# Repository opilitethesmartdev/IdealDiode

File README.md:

# Ideal Diode
Author: opilitethesmartdev

This is a small PCB featuring an ideal diode emulator using a comparator and a P-MOSFET.

# Principle

1. It uses two diodes to let power in from any side without connecting them, used to feed the comparator and the voltages for the MOSFETS
2. a P-MOS sits between the diodes, with its internal diode directed at the side to be blocked.
3. This P-MOS is pulled high by the same two diodes from #1
4. An N-MOS sits below the P-MOS gate, and will pull it down when activated (turning the P-MOS on)
5. A comparator compares the two sides, and when the forward side is higher than the reverse side, it pulls its output high,
activating the N-MOS, which pulls the P-MOS down, which lets current flow

# Performance
The performance of such constructs is dependent on the P-MOS they use - for simulation, I have used the specs of an DMP3099L P-MOS
(~100mOhm Rdson at -5V), which yield about a 0.1V drop at 1A current - much lower for smaller currents.
However, this PCB component uses the AO3401A, which has a much lower RDSon (about 45 mOhm at the same voltage)

# Simulation
I used Falstad for the simulation. [Here is the link](https://www.falstad.com/circuit/circuitjs.html?ctz=DwYwlgTgBAZgvAIgIwKgFwM6IAwDpsEECsqYIiSeATAVQOx0DM2AHFQGwCcndqIARoiLZUAB0EIALI1QA3CENQBbTEICmAWiQoAfACgoUYAHcoAD0RN2UFpJZQrNliNg4EAen2HgAYQD2SqIAhhBBaH7QFgjskthOcTFxLEjsqPDIHl5GplFEdNZ0NFCJDjRpbp4GRgAm5pbs9oVx+fbsheUILkp+iNVqMEEArgA2aJlVwLW5+aVxedZtVB1dPQh9AyNjld45iHbNRURIVLPL4zt1CM4HSTGnrp3n2ZclTcVEBWUPItvPUXTYSSzBwNe7pH5ZYAAc0ujhYzgcjGsLE4qW+T2ASiUUAAdkpEABBAAKzgActgqKSAGJnKCyNA4XDsEhQfhqSySVAYCQoKDVDAATzcrOqFFQ-AZjyg3NFGV+wBgsMBNkYJzhqtp3UJJOw5MpNPluyudzothsJq+4IxRoajSKAKBTTOhsuRzVh0kjstFUhRs9dri+zBPomftVwP9wceLqikbecdszshMNjdnNQMj8JcVvlkT2adNGbTLA16KgCikGIAMgBRAAil0z4czMU1q3WQ1GGmGamqfArvJAUOFAmFSn45E6+BQ8oASpdOMdgZxPVGUqhjFaoEogmZZIooJBFPKMJcWBa4ov3dnhaIxfLaw2ouegSWTi-023ev1O2hu73+zFKAhxHCQugnRlsBnSE82NR0zQ-N9aQrTl5RTRBELuRDnCTCZ5yiRgzTeRgiGvDp1ygTcx13fcEBZI86IxU8CKIoppDIss7zlSEsVxfEEDrABZIlmG4KtaXpIC2UQGRpR5VB+SFKV+FlXkJWFGV70hRUokWBxSOKQo12UVYhJE7AxOtV0Zj0ohOBOZk0RzX1YVBPS6AMxzcIuf5PI+YpWHeJyQx8xB2ECxyoDshyPm8v4woi-zwsaBo4pMF4jI8hzMtS9EYzCnLGiREEWDSo1HBaRFkQo5yJlgyLKteXKtwHQgrN0-zGsKsqXliEqApS0q8pg3qkgIYoqFfAhkIoNr8uiPrkgWRbpuG0MXkmmxxuSrab2jFzdMC64BpKnrdMWlJinhGwapC+LomuparvsJC1tCh6XvDB0VSWN77vYTaswmoErzOsLNqvKLV1Bv70tyaGlyIVcnVho15mBJGvT2iF1o65EEUimHavewml2Oom7rhjDxsh46UeJ+66ftUF6ZDYB3HACB9CAA)

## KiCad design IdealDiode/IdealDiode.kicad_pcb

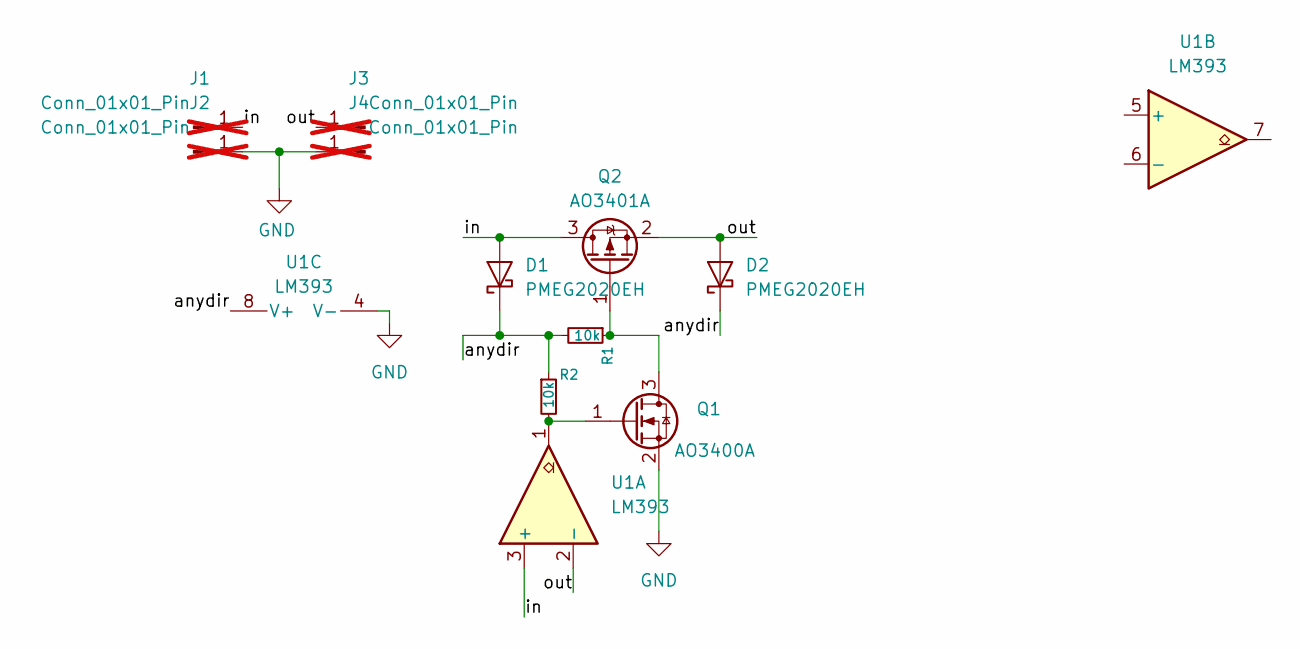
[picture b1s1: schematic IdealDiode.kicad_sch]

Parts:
D1, D2: PMEG2020EH; D_DO-41_SOD81_P10.16mm_Horizontal; LCSC Part # C52287409
J1, J2, J3, J4: Conn_01x01_Pin; PinHeader_1x01_P2.54mm_Vertical; not fitted
Q1: AO3400A; SOT-23; LCSC Part # C20917
Q2: AO3401A; SOT-23; LCSC Part # C15127
R1, R2: 10k; R_Axial_DIN0207_L6.3mm_D2.5mm_P7.62mm_Horizontal; LCSC Part # C25531
U1: LM393; DIP-8_W7.62mm

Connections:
/anydir: D1.1 (K), D2.1 (K), R1.2, R2.1, U1.8 (V+)
/in: D1.2 (A), J1.1 (Pin_1_1), Q2.3 (D), U1.3 (+)
/out: D2.2 (A), J3.1 (Pin_1_1), Q2.2 (S), U1.2 (-)
GND: J2.1 (Pin_1_1), J4.1 (Pin_1_1), Q1.2 (S), U1.4 (V-)
unnamed: Q1.3 (D), Q2.1 (G), R1.1
unnamed: Q1.1 (G), R2.2, U1.1

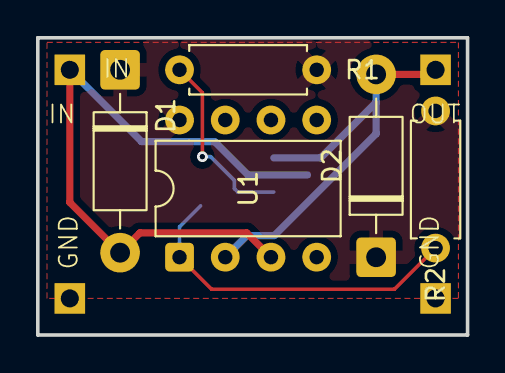
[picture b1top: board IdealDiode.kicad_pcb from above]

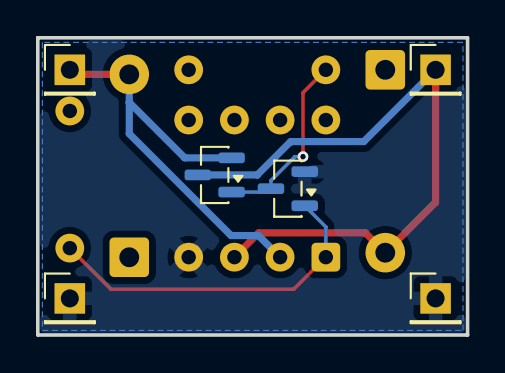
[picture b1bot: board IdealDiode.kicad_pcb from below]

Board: 2 copper layers, 23.9 x 16.5 mm, 11 parts (6 on the bottom side), 6 nets.

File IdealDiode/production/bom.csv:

Designator,Footprint,Quantity,Value,LCSC Part #
"D1, D2",D_SOD-123F,2,PMEG2020EH,C52287409
"J1, J2, J3, J4",PinHeader_1x01_P2.54mm_Vertical,4,Conn_01x01_Pin,
Q1,SOT-23,1,AO3400A,C20917
Q2,SOT-23,1,AO3401A,C15127
"R1, R2",0402,2,10k,C25531
U1,VSSOP-8_3x3mm_P0.65mm,1,LM393,C34440
